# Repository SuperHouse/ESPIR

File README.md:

ESPIR: PIR motion sensor with ESP8266
=====================================

Copyright 2017-2020 SuperHouse Automation Pty Ltd  www.superhouse.tv  

Motion detector using a PIR and an ESP8266.

Features:

 * ESP8266 MCU with wifi.
 * Efficient 3.3V switchmode power supply.

More information is available at:

  http://www.superhouse.tv/espir

INSTALLATION
------------
The design is saved as an EAGLE project. EAGLE PCB design software is
available from www.cadsoftusa.com free for non-commercial use. To use
this project download it and place the directory containing these files
into the "eagle" directory on your computer.

DISTRIBUTION
------------
The specific terms of distribution of this project are governed by the
license referenced below.

LICENSE
-------
Licensed under the TAPR Open Hardware License (www.tapr.org/OHL).
The "license" folder within this repository also contains a copy of
this license in plain text format.

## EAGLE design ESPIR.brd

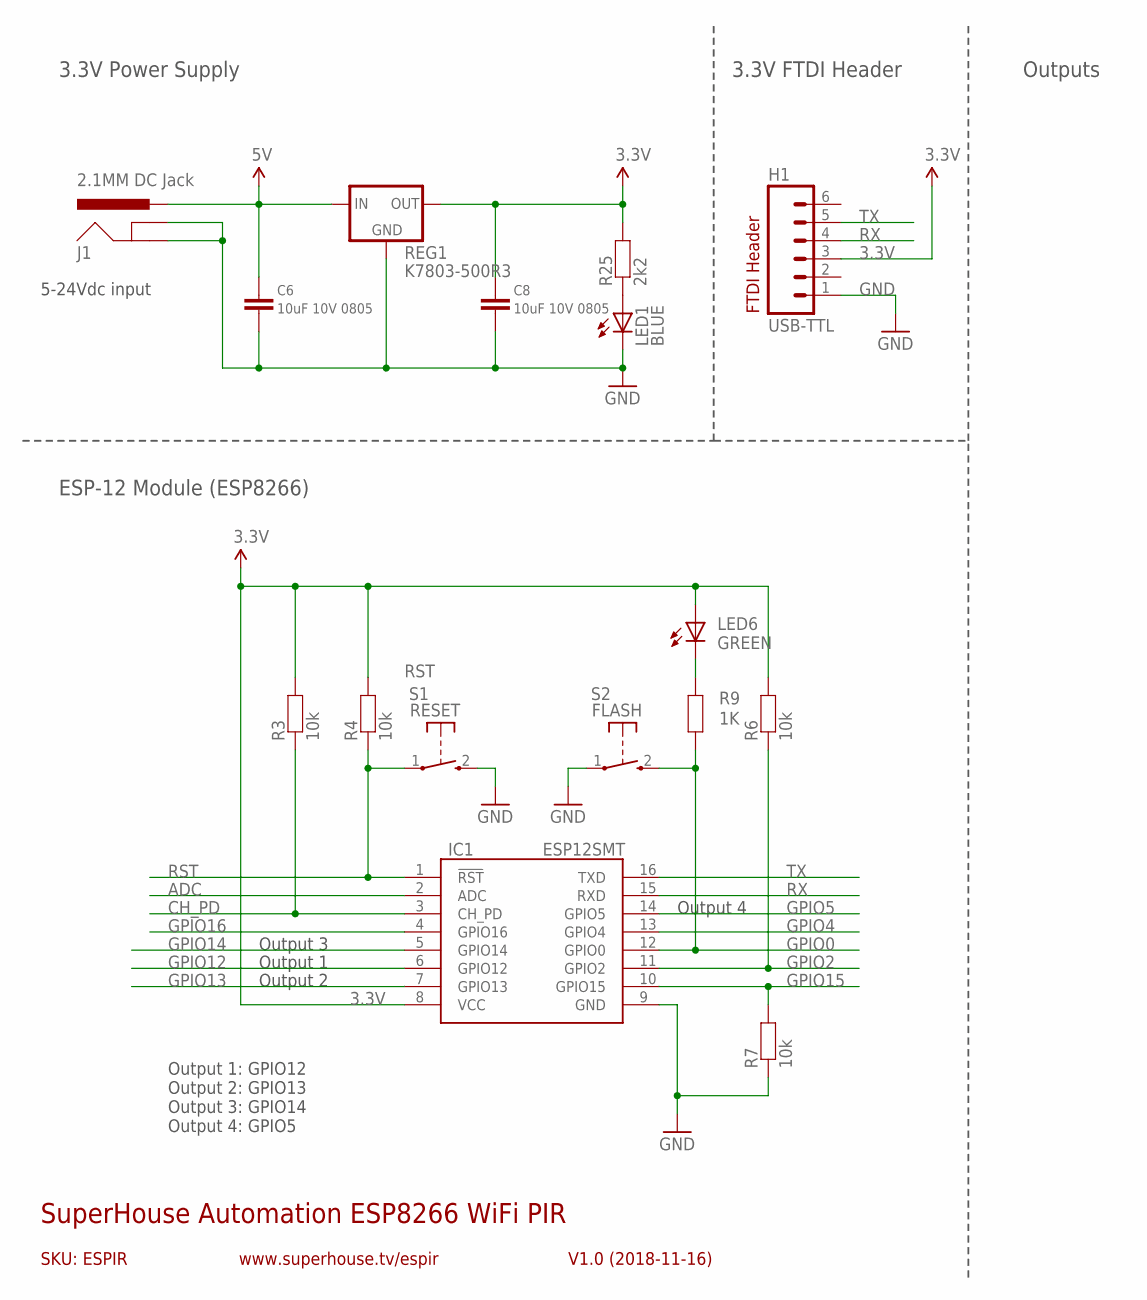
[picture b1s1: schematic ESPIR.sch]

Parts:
C6, C8: 10uF 10V 0805; C0805
H1: USB-TTL; 1X06
IC1: ESP12SMT; ESP12
J1: 2.1MM DC Jack; POWER_JACK_PTH_SLOTS
LED1: BLUE; LED-0603
LED6: GREEN; LED-0603
R3, R4, R6, R7: 10k; 0603
R9: 1K; 0603
R25: 2k2; 0603
REG1: K7803-500R3; K78XX-500R3
S1: RESET; TACTILE_SWITCH_SMD_2PIN_TINY
S2: FLASH; TACTILE_SWITCH_SMD_2PIN_TINY

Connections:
3.3V: C8.1, H1.3, IC1.8 (VCC), LED6.A, R3.2, R4.2, R6.2, R25.2, REG1.3 (OUT)
5V: C6.1, J1.PWR, REG1.1 (IN)
ADC: IC1.2 (ADC)
CH_PD: IC1.3 (CH_PD), R3.1
GND: C6.2, C8.2, H1.1, IC1.9 (GND), J1.GND, J1.GNDBREAK, LED1.C, R7.1, REG1.2 (GND), S1.2 (S), S2.1
GPIO0: IC1.12 (GPIO0), R9.2, S2.2 (S)
GPIO2: IC1.11 (GPIO2), R6.1
GPIO4: IC1.13 (GPIO4)
GPIO5: IC1.14 (GPIO5)
GPIO12: IC1.6 (GPIO12)
GPIO13: IC1.7 (GPIO13)
GPIO14: IC1.5 (GPIO14)
GPIO15: IC1.10 (GPIO15), R7.2
GPIO16: IC1.4 (GPIO16)
unnamed: LED1.A, R25.1
unnamed: LED6.C, R9.1
RST: IC1.1 (!RST), R4.1, S1.1
RX: H1.4, IC1.15 (RXD)
TX: H1.5, IC1.16 (TXD)

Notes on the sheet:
SKU: ESPIR
SuperHouse Automation ESP8266 WiFi PIR
V1.0 (2018-11-16)
www.superhouse.tv/espir
3.3V Power Supply
FTDI Header
Outputs
ESP-12 Module (ESP8266)
3.3V FTDI Header
5-24Vdc input
Output 1: GPIO12 Output 2: GPIO13 Output 3: GPIO14 Output 4: GPIO5
Output 1
Output 2
Output 3
Output 4

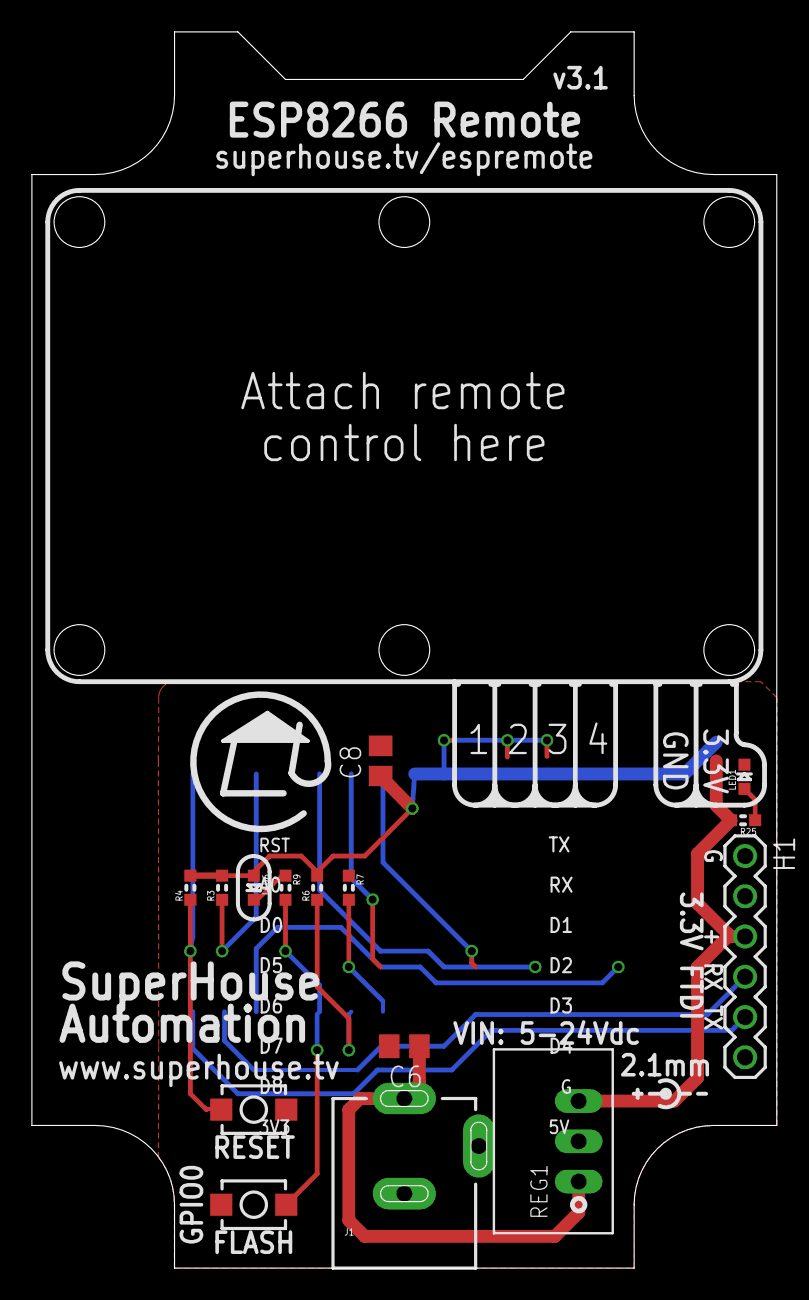
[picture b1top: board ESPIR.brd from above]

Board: 2 copper layers, 47.0 x 78.0 mm, 16 parts (1 on the bottom side), 12 nets.

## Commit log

2020-03-18 Initial import, taken from ESPREMOTE project

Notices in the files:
ESPIR.brd:
(C)2017 SuperHouse
Hardware Licence: tapr.org/ohl
parts and their libraries:
freetronics-original: Licensing: CC v3.0 Share-Alike You are welcome to use this library for commercial purposes.
